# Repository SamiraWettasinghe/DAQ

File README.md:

# DAQ
Open source data acquisition system designed for the grassroots motorsports enthusiast.

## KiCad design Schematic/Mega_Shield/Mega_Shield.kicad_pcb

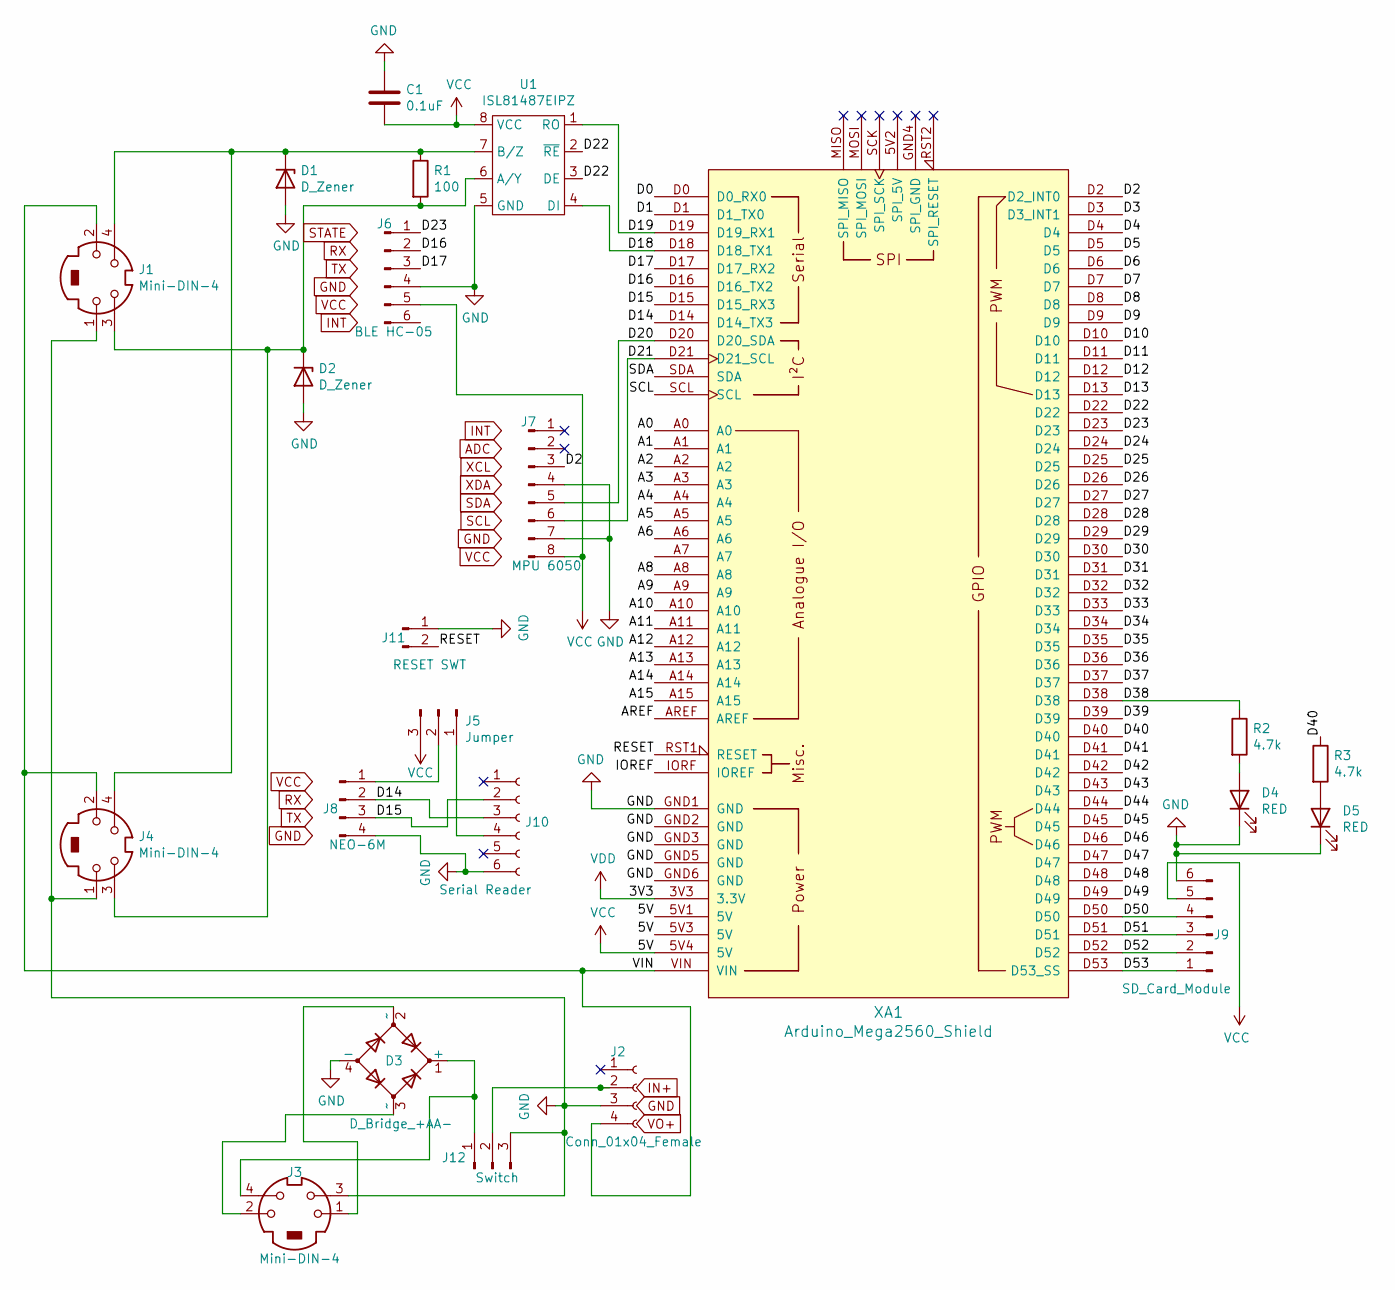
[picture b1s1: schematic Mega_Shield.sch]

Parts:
C1: 0.1uF; C_Rect_L4.0mm_W2.5mm_P2.50mm
D1, D2: D_Zener; D_DO-41_SOD81_P10.16mm_Horizontal
D3: D_Bridge_+AA-; KBP306GTB
D4, D5: RED; LED_3mm_Radial
J1, J3, J4: Mini-DIN-4; PinSocket_2x02_P2.54mm_Vertical
J2: Conn_01x04_Female; Voltage_Regulator
J5: Jumper; PinSocket_1x03_P2.54mm_Vertical
J6: BLE HC-05; BLEHC-05
J7: MPU 6050; GY-521
J8: NEO-6M
J9: SD_Card_Module; SD_Module_Vertical
J10: Serial Reader; PinSocket_1x06_P2.54mm_Vertical
J11: RESET SWT; PinSocket_1x02_P2.54mm_Vertical
J12: Switch; PinSocket_1x03_P2.54mm_Vertical
R1: 100; R_Axial_DIN0207_L6.3mm_D2.5mm_P7.62mm_Horizontal
R2, R3: 4.7k; R_Axial_DIN0204_L3.6mm_D1.6mm_P5.08mm_Horizontal
U1: ISL81487EIPZ; ISL81487EIPZ-PDIP
XA1: Arduino_Mega2560_Shield

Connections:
/A0: XA1.A0
/A1: XA1.A1
/A2: XA1.A2
/A3: XA1.A3
/A4: XA1.A4
/A5: XA1.A5
/A6: XA1.A6
/A8: XA1.A8
/A9: XA1.A9
/A10: XA1.A10
/A11: XA1.A11
/A12: XA1.A12
/A13: XA1.A13
/A14: XA1.A14
/A15: XA1.A15
/AREF: XA1.AREF
/D0: XA1.D0 (D0_RX0)
/D1: XA1.D1 (D1_TX0)
/D2: J7.3, XA1.D2 (D2_INT0)
/D3: XA1.D3 (D3_INT1)
/D4: XA1.D4
/D5: XA1.D5
/D6: XA1.D6
/D7: XA1.D7
/D8: XA1.D8
/D9: XA1.D9
/D10: XA1.D10
/D11: XA1.D11
/D12: XA1.D12
/D13: XA1.D13
/D14: J8.2, J10.3, XA1.D14 (D14_TX3)
/D15: J8.3, J10.2, XA1.D15 (D15_RX3)
/D16: J6.2, XA1.D16 (D16_TX2)
/D17: J6.3, XA1.D17 (D17_RX2)
/D18: U1.4 (DI), XA1.D18 (D18_TX1)
/D19: U1.1 (RO), XA1.D19 (D19_RX1)
/D20: J7.5, XA1.D20 (D20_SDA)
/D21: J7.6, XA1.D21 (D21_SCL)
/D22: U1.2 (~RE), U1.3 (DE), XA1.D22
/D23: J6.1, XA1.D23
/D24: XA1.D24
/D25: XA1.D25
/D26: XA1.D26
/D27: XA1.D27
/D28: XA1.D28
/D29: XA1.D29
/D30: XA1.D30
/D31: XA1.D31
/D32: XA1.D32
/D33: XA1.D33
/D34: XA1.D34
/D35: XA1.D35
/D36: XA1.D36
/D37: XA1.D37
/D38: R2.1, XA1.D38
/D39: XA1.D39
/D40: R3.1, XA1.D40
/D41: XA1.D41
/D42: XA1.D42
/D43: XA1.D43
/D44: XA1.D44
/D45: XA1.D45
/D46: XA1.D46
/D47: XA1.D47
/D48: XA1.D48
/D49: XA1.D49
/D50: J9.4, XA1.D50
/D51: J9.3, XA1.D51
/D52: J9.2, XA1.D52
/D53: J9.1, XA1.D53 (D53_SS)
/IOREF: XA1.IORF (IOREF)
/RESET: J11.2, XA1.RST1 (RESET)
/VIN: J1.2, J2.4, J4.2, XA1.VIN
GND: C1.1, D1.2 (A), D2.2 (A), D3.4 (-), D4.1 (K), D5.1 (K), J1.1, J2.3, J3.3, J4.1, J6.4, J7.4, J7.7, J8.4, J9.6, J10.6, J11.1, J12.3, U1.5 (GND), XA1.GND1 (GND), XA1.GND2 (GND), XA1.GND3 (GND), XA1.GND5 (GND), XA1.GND6 (GND)
unnamed: D1.1 (K), J1.4, J4.4, R1.1, U1.7 (B/Z)
unnamed: D2.1 (K), J1.3, J4.3, R1.2, U1.6 (A/Y)
unnamed: D3.1 (+), J3.4, J12.1
unnamed: D3.2 (~~), J3.1
unnamed: D3.3 (~~), J3.2
unnamed: D4.2 (A), R2.2
unnamed: D5.2 (A), R3.2
unnamed: J5.2, J8.1
unnamed: J5.1, J10.4
unnamed: J2.2, J12.2
SCL: XA1.SCL
SDA: XA1.SDA
VCC: C1.2, J5.3, J6.5, J7.8, J9.5, U1.8 (VCC), XA1.5V1 (5V), XA1.5V3 (5V), XA1.5V4 (5V)
VDD: XA1.3V3 (3.3V)

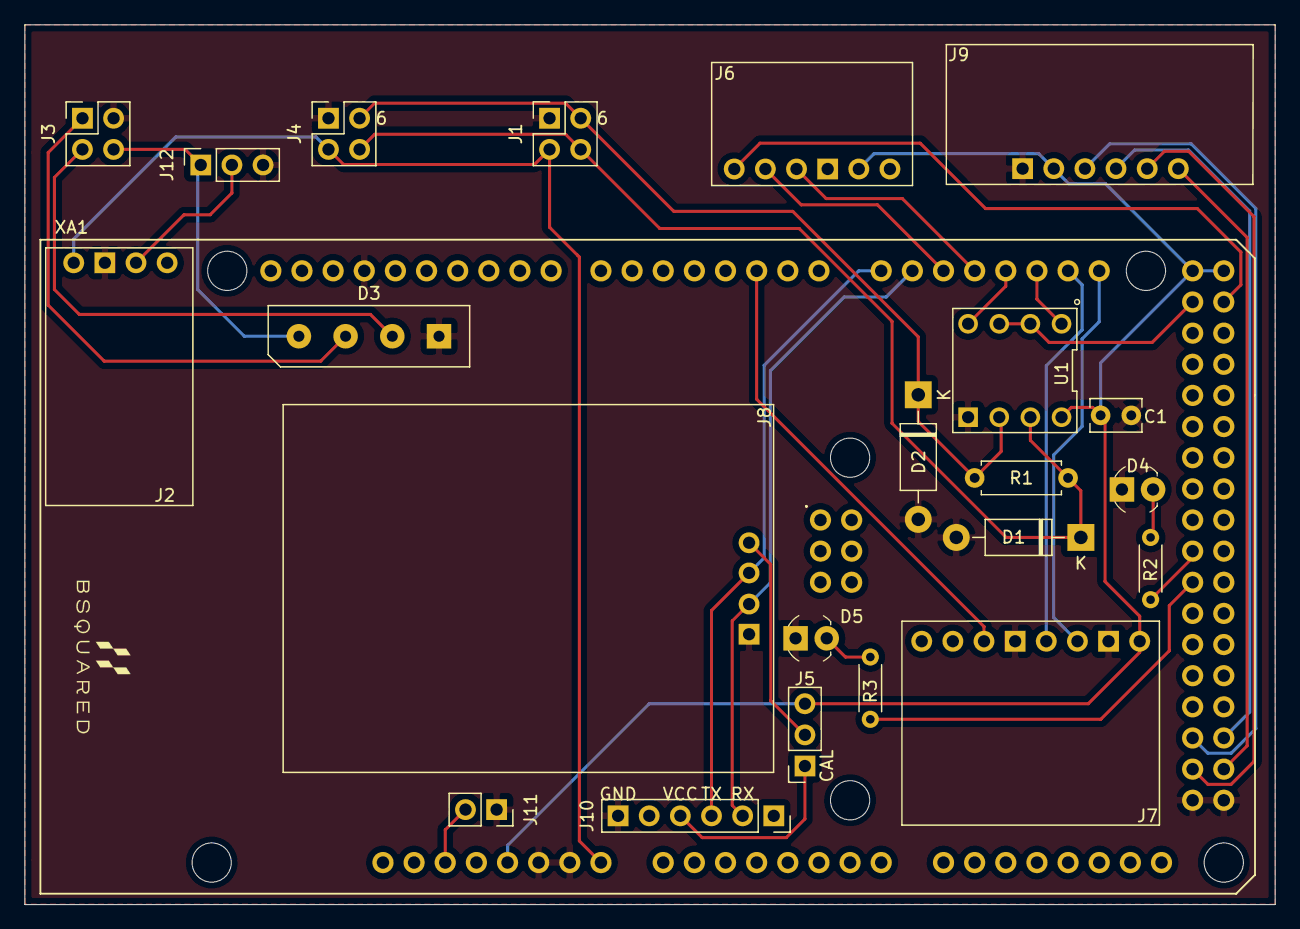
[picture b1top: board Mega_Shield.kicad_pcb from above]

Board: 2 copper layers, 102.0 x 71.8 mm, 23 parts (0 on the bottom side), 31 nets.

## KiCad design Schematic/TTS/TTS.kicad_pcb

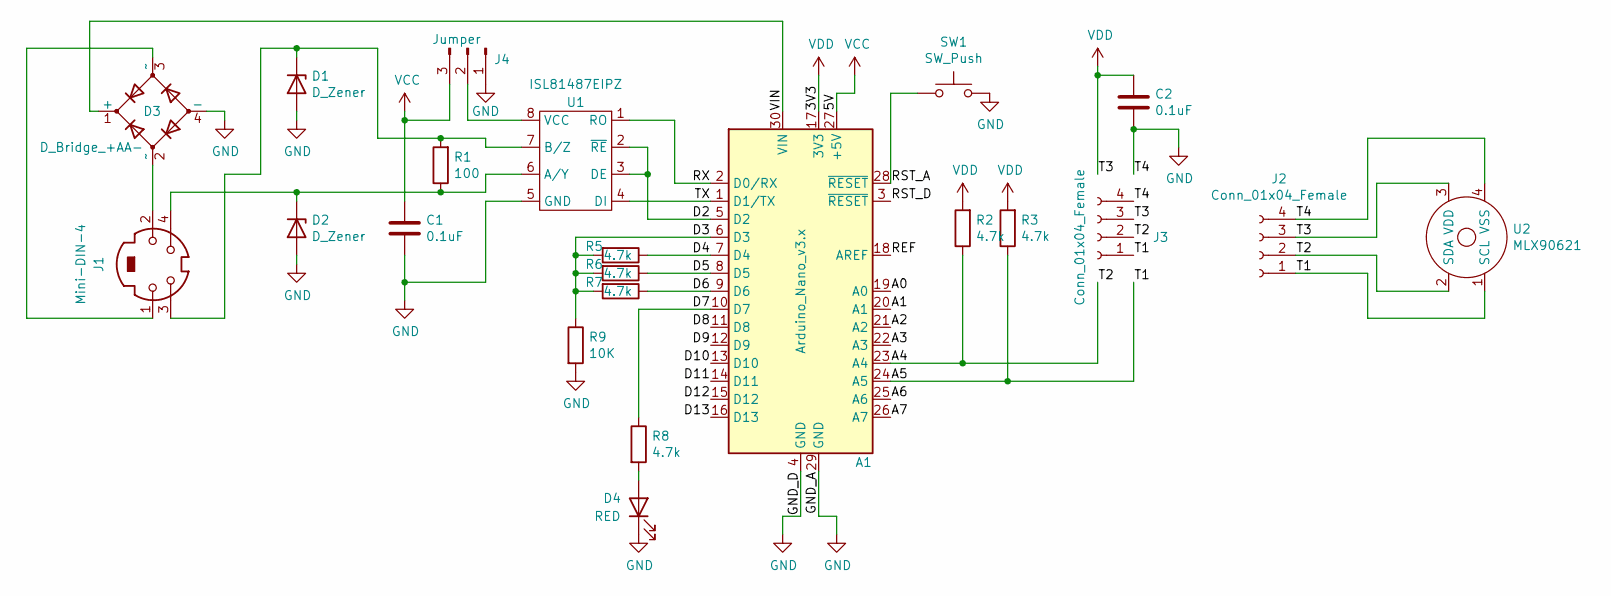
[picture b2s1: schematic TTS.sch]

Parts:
A1: Arduino_Nano_v3.x; Arduino_Nano
C1, C2: 0.1uF; C_Rect_L4.0mm_W2.5mm_P2.50mm
D1, D2: D_Zener; D_DO-41_SOD81_P10.16mm_Horizontal
D3: D_Bridge_+AA-; KBP306GTB
D4: RED; LED_3mm_Radial
J1: Mini-DIN-4; PinSocket_2x02_P2.54mm_Vertical
J2, J3: Conn_01x04_Female; PinSocket_1x04_P2.54mm_Vertical
J4: Jumper; PinSocket_1x03_P2.54mm_Vertical
R1: 100; R_Axial_DIN0309_L9.0mm_D3.2mm_P12.70mm_Horizontal
R2, R3, R5, R6, R7, R8: 4.7k; R_Axial_DIN0204_L3.6mm_D1.6mm_P5.08mm_Horizontal
R9: 10K; R_Axial_DIN0207_L6.3mm_D2.5mm_P7.62mm_Horizontal
SW1: SW_Push; PinSocket_1x02_P2.54mm_Vertical
U1: ISL81487EIPZ; ISL81487EIPZ-PDIP
U2: MLX90621; MLX90614ESF-BCC-000-TU

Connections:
/A0: A1.19 (A0)
/A1: A1.20 (A1)
/A2: A1.21 (A2)
/A3: A1.22 (A3)
/A4: A1.23 (A4), J2.2, J3.2, R2.1, U2.2 (SDA)
/A5: A1.24 (A5), J2.1, J3.1, R3.1, U2.1 (SCL)
/A6: A1.25 (A6)
/A7: A1.26 (A7)
/D2: A1.5 (D2), U1.2 (~RE), U1.3 (DE)
/D3: A1.6 (D3), R5.2, R6.2, R7.2, R9.1
/D4: A1.7 (D4), R5.1
/D5: A1.8 (D5), R6.1
/D6: A1.9 (D6), R7.1
/D7: A1.10 (D7), R8.1
/D8: A1.11 (D8)
/D9: A1.12 (D9)
/D10: A1.13 (D10)
/D11: A1.14 (D11)
/D12: A1.15 (D12)
/D13: A1.16 (D13)
/REF: A1.18 (AREF)
/RST_A: A1.28 (~RESET), SW1.1
/RST_D: A1.3 (~RESET)
/RX: A1.2 (D0/RX), U1.1 (RO)
/TX: A1.1 (D1/TX), U1.4 (DI)
/VIN: A1.30 (VIN), D3.1 (+)
GND: A1.4 (GND), A1.29 (GND), C1.2, C2.2, D1.2 (A), D2.2 (A), D3.4 (-), D4.1 (K), J2.4, J3.4, J4.1, R9.2, SW1.2, U1.5 (GND), U2.4 (VSS)
unnamed: D1.1 (K), J1.3, R1.2, U1.7 (B/Z)
unnamed: D2.1 (K), J1.4, R1.1, U1.6 (A/Y)
unnamed: D3.2 (~~), J1.2
unnamed: D3.3 (~~), J1.1
unnamed: D4.2 (A), R8.2
unnamed: J4.2, U1.8 (VCC)
VCC: A1.27 (+5V), C1.1, J4.3
VDD: A1.17 (3V3), C2.1, J2.3, J3.3, R2.2, R3.2, U2.3 (VDD)

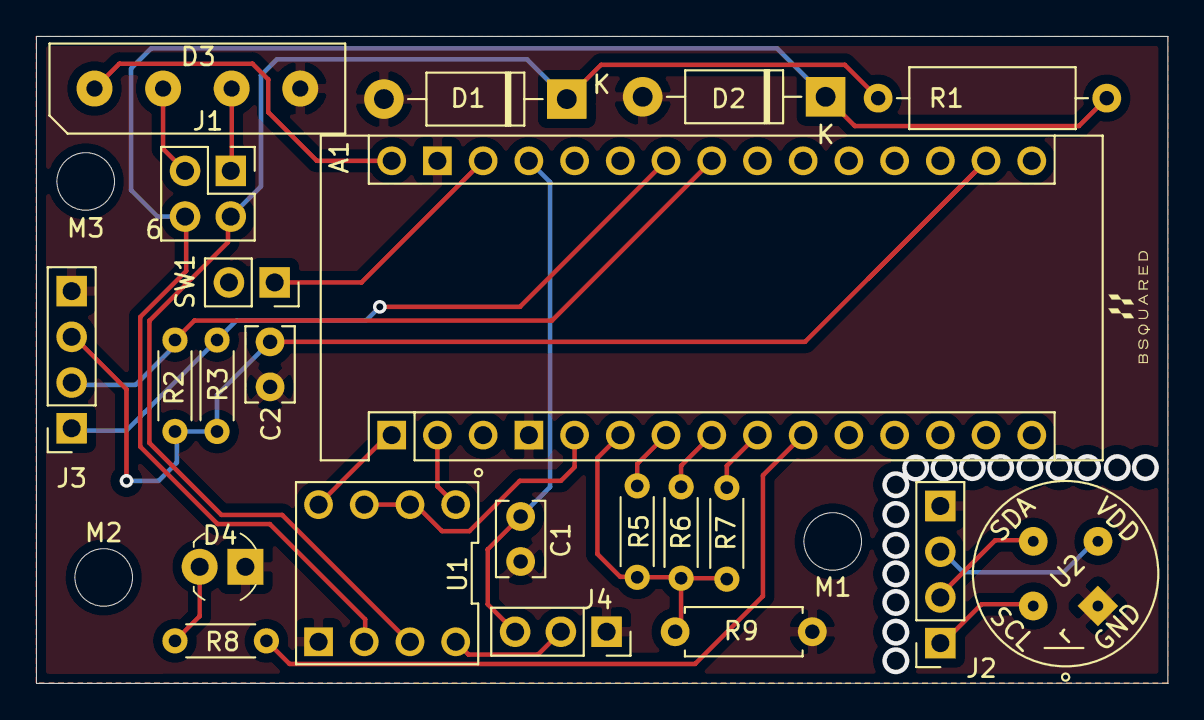
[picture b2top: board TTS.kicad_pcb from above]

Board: 2 copper layers, 62.9 x 35.9 mm, 25 parts (0 on the bottom side), 21 nets.

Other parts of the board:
M1, M2, M3: MountingHole_3.2mm_M3

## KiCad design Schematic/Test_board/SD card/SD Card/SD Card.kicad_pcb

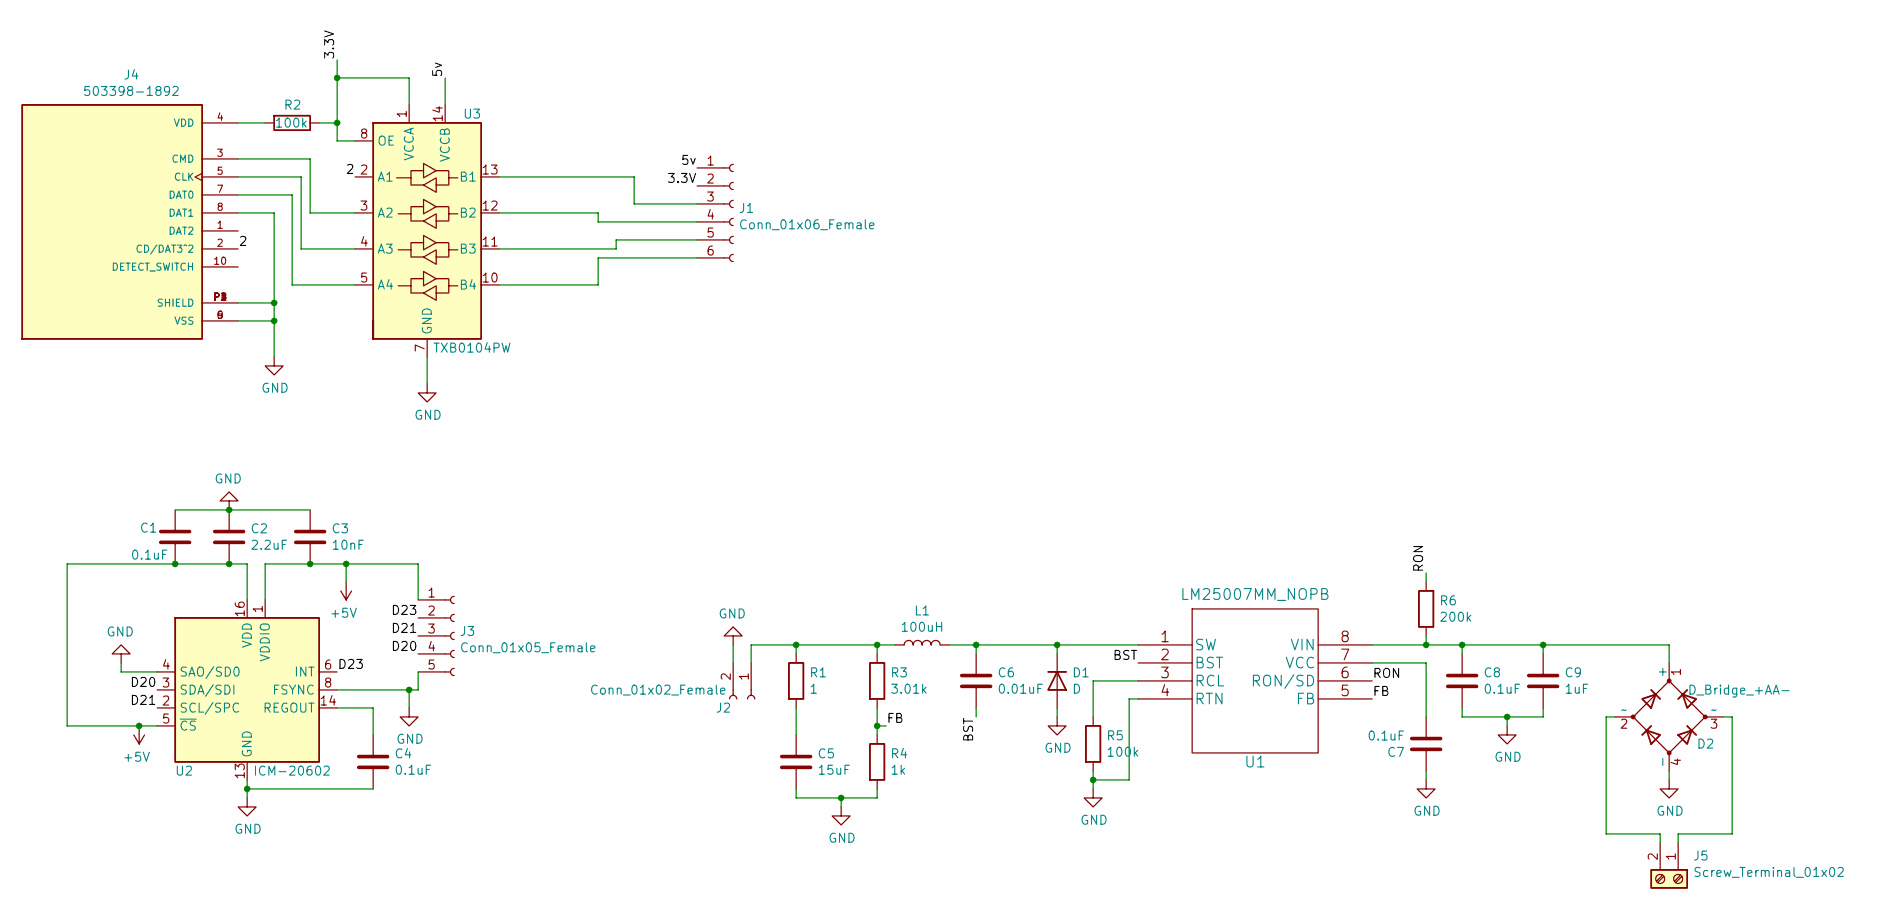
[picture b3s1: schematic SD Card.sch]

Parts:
C1, C4: 0.1uF; CP_Radial_D5.0mm_P2.50mm
C2: 2.2uF; CP_Radial_D5.0mm_P2.50mm
C3: 10nF; CP_Radial_D5.0mm_P2.50mm
C5: 15uF; C_1812_4532Metric_Pad1.57x3.40mm_HandSolder
C6: 0.01uF; C_1206_3216Metric_Pad1.33x1.80mm_HandSolder
C7, C8: 0.1uF; C_1206_3216Metric_Pad1.33x1.80mm_HandSolder
C9: 1uF; C_1812_4532Metric_Pad1.57x3.40mm_HandSolder
D1: D; D_SMA_Handsoldering
D2: D_Bridge_+AA-; KBP306GTB
J1: Conn_01x06_Female; PinHeader_1x06_P2.54mm_Vertical
J2: Conn_01x02_Female; PinHeader_1x02_P2.54mm_Vertical
J3: Conn_01x05_Female; PinHeader_1x05_P2.54mm_Vertical
J4: 503398-1892; MOLEX_503398-1892; PARTREV 0
J5: Screw_Terminal_01x02; TerminalBlock_Phoenix_PT-1,5-2-5.0-H_1x02_P5.00mm_Horizontal
L1: 100uH; L_TDK_SLF7045
R1: 1; R_1206_3216Metric_Pad1.30x1.75mm_HandSolder
R2: 100k; R_Axial_DIN0204_L3.6mm_D1.6mm_P5.08mm_Horizontal
R3: 3.01k; R_1206_3216Metric_Pad1.30x1.75mm_HandSolder
R4: 1k; R_1206_3216Metric_Pad1.30x1.75mm_HandSolder
R5: 100k; R_1206_3216Metric_Pad1.30x1.75mm_HandSolder
R6: 200k; R_1206_3216Metric_Pad1.30x1.75mm_HandSolder
U1: LM25007MM_NOPB; LM25007MM&slash_NOPB
U2: ICM-20602; LGA-16_3x3mm_P0.5mm_LayoutBorder3x5y
U3: TXB0104PW; TSSOP-14_4.4x5mm_P0.65mm

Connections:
+5V: C1.2, C2.2, C3.2, J3.1, U2.1 (VDDIO), U2.5 (~CS), U2.16 (VDD)
/2: J4.2 (CD/DAT3^2), U3.2 (A1)
/3.3V: J1.2, R2.1, U3.1 (VCCA), U3.8 (OE)
/5v: J1.1, U3.14 (VCCB)
/BST: C6.2, U1.2 (BST)
/D20: J3.4, U2.3 (SDA/SDI)
/D21: J3.3, U2.2 (SCL/SPC)
/D23: J3.2, U2.6 (INT)
/FB: R3.2, R4.1, U1.5 (FB)
/RON: R6.2, U1.6 (RON/SD)
GND: C1.1, C2.1, C3.1, C4.2, C5.2, C7.1, C8.2, C9.2, D1.2 (A), D2.4 (-), J2.2, J3.5, J4.6 (VSS), J4.8 (DAT1), J4.9 (VSS), J4.P1 (SHIELD), J4.P2 (SHIELD), J4.P3 (SHIELD), J4.P4 (SHIELD), R4.2, R5.2, U1.4 (RTN), U2.4 (SAO/SD0), U2.8 (FSYNC), U2.9 (GND), U2.10 (GND), U2.11 (GND), U2.12 (GND), U2.13 (GND), U2.15 (GND), U3.7 (GND)
unnamed: C4.1, U2.14 (REGOUT)
unnamed: C5.1, R1.2
unnamed: C6.1, D1.1 (K), L1.2, U1.1 (SW)
unnamed: C7.2, U1.7 (VCC)
unnamed: C8.1, C9.1, D2.1 (+), R6.1, U1.8 (VIN)
unnamed: D2.2 (~~), J5.2
unnamed: D2.3 (~~), J5.1
unnamed: J1.3, U3.13 (B1)
unnamed: J1.4, U3.12 (B2)
unnamed: J1.5, U3.11 (B3)
unnamed: J1.6, U3.10 (B4)
unnamed: J2.1, L1.1, R1.1, R3.1
unnamed: J4.3 (CMD), U3.3 (A2)
unnamed: J4.4 (VDD), R2.2
unnamed: J4.5 (CLK), U3.4 (A3)
unnamed: J4.7 (DAT0), U3.5 (A4)
unnamed: R5.1, U1.3 (RCL)

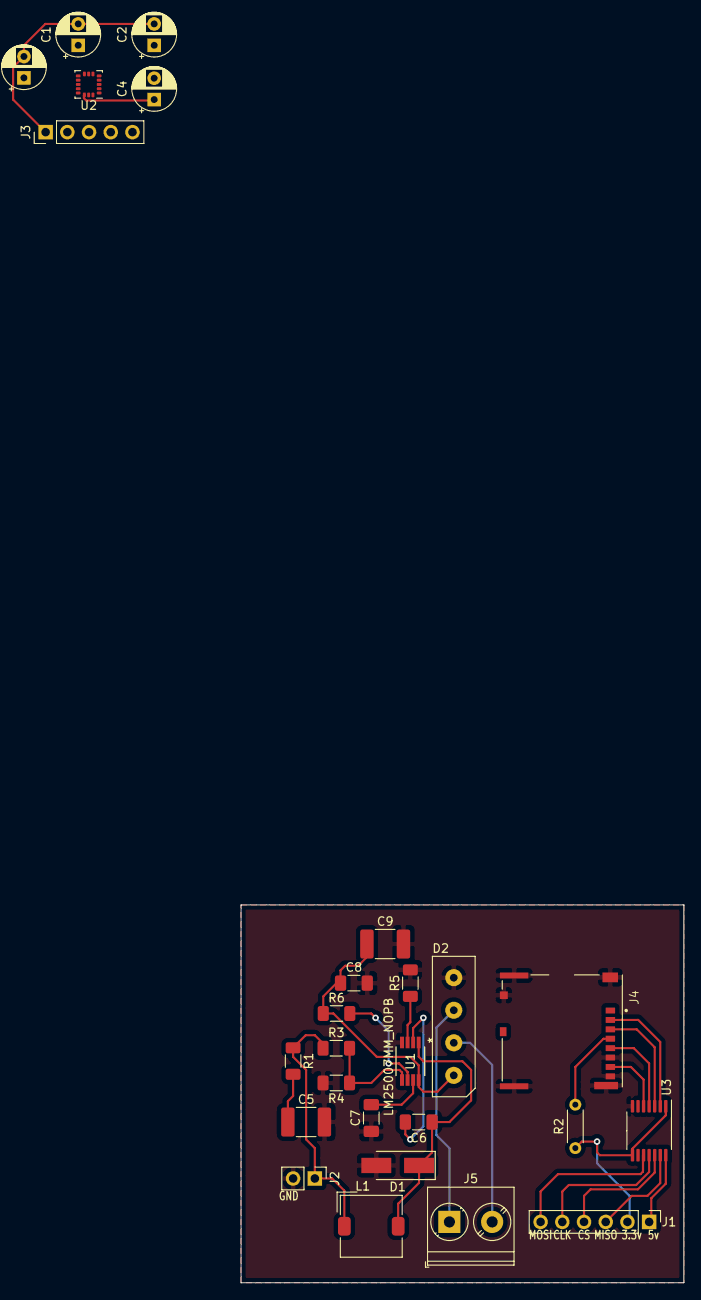
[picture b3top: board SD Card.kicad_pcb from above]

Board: 2 copper layers, 51.8 x 44.2 mm, 26 parts (0 on the bottom side), 28 nets.

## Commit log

2020-08-13 Added OBDii data.
    Through OBD, added capability to read vehicle speed and RPM. Work still needs to be done to send CAN frames to Mega successfully. OBD is accessed through Sparkfun's UART.
    Vehicle CAN Project - Investigation
2020-08-18 Initial commit of accelerometer code.
    Added code to interface to MPU-6050. Code is from playgroud.arduino.cc/Main/MPU-6050. Raw values of accel, gyro, and temperature are recorded and sent through serial monitor.
    Accelerometer investigation
2020-08-19 Added CAN communication for OBD-II data.
    Modified obdii file to send vehicle speed and RPM over CAN. Also added code on receive module to receive CAN data from obdii module. CAN ID for obdii is 0x05.
    OBD-II Data Integration
2020-08-20 Added dual accelerometer comms
    Set up ADO pin to ground for one sensor and 3.3V for the other sensor such that the sensors can have different addresses (0x68 and 0x69).
    Accelerometer and Gyrometer Investigation
2020-08-21 GPS and SD card data logger
    Ubloc Neo-6m GPS module is used - Pin 2 and 3 is as TX and RX reader
    Mirco SD card adapter module is connected with the following Pin IDs Vcc to 5v, MISO to pin 12 (50), MOSI to Pin 11 (51), SCK to pin 13 (52) and CS to Pin 4 (53). Note for Arduino UNO use Pin ID with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
2020-08-21 Organization and documentation and added CAN comms
    Created GPS folder to store the GPS code. Created integration documentation for accelerometer and the OBD-II data. Added CAN comms for the accelerometer data. 0x06 for linear acceleration and 0x07 fo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
    Accelerometer and Gyrometer Investigation
2020-09-15 Added SD Card integration.
    SD card is commmunicating via UART with Mega. Currently sending only accelerometer data.
    First evaluation day - Samira Wettasinghe
2020-09-17 Changed to SPI comms for SD card
    SPI comms working for SD card storage. No issues since CS is D11 while tire temps are on D12.
    SD Card Comms - Samira Wettasinghe
2020-09-21 Added timestamp
    CAN transmits timestamp. SD card will store timestamp in hour minute millisecond format.
    Timestamp transmission - Samira Wettasinghe
2020-09-22 Tire temp timestamp coherency
    Added simple coherency check.
    Modified delays to be as short as possible to avoid filling the buffer.
    Created functions to clean up code.
    Timestamp transmission - Samira Wettasinghe
2020-09-26 Integrated GPS code. General cleanup.
    GPS code is integrated. Added hardware present calibrations. Cleaned up code to ensure that it works properly when all sensors are presnet. Removed some of the time stamp coherency checks for now, ad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
    Installation Day 2 - Samira Wettasinghe
2020-09-29 Fixed OBD logging. Added system arch doc.
    OBD logging now done properly and logging quickly. Created initial revision of architecture document. Feature revisions made for Mega code as well.
    V2 Testing - Samira Wettasinghe
2020-10-25 Added PCB designs
    Adding PCB design of Mega shield and tire temp sensors.
    Samira Wettasinghe
2020-10-30 Antul is amazing
    Antul literally is so smart. Everytime we have an issue, and he has a suggestion, he is always correct. Amando agrees.
    Preach Antul - Samira Wettasinghe
2020-10-30 Git Training
    Useful File
    Git Training - Samira Wettasinghe
2020-10-30 Git training
2020-11-12 Updating schematic with Oshpark/Digikey order
    Updates to add various components and capability.
    2.2 Basic Sensor Suite
2020-11-12 Differential wire concept
    Testing concept with serial comms.
    2.2 Basic Sensor Suite
2020-11-17 DIP switch and status LED and IMU code integrated
    Added code to read from DIP switch and LED digital pins. IMU code added on mega shield. No data can be read on the i2c due to incorrect SCL/SDA pins being connected to IMU.
    2.2 Basic Sensor Suite
2020-11-18 SD Card logging code added.
    SD card logic was added. CS may need modification based on new PCB design. This code will need to be tested.
    2.2 Basic Sensor Suite
2020-11-20 Fixed schematic issues. Made code for TTS transmit
    Schematic issues documented on Trello card fixed. TTS differential wire transmit code for the TTS implemented. Still need to do auto adressing and time stamp transmission.
    2.2 Basic Sensor Suite
2020-12-03 Verified UART comms.
    Made sure that UART was working with two sensors communicating with Mega.
    2.2 Basic Sensor Suite
2020-12-10 Integration of IMU + comms algo upgrade.
    Upgraded comms method to use switch/case method. Integrade the IMU board onto the Mega shield.
    2.2 Basic Sensor Suite
2020-12-15 Added diagnostic messages and error codes
    Added serial data print messages if data received doesn't make sense.
    Added error codes that will print to the data.
    Added LED for indicate an error has set.
    2.7 Diagnostic Software
2020-12-16 test board PCB design
    PCB include SD card and IMU
    2.2 Basic Sensor Suite
2020-12-17 test board PCB design
    PCB includes SD card and IMU
    2.2 Basic Sensor Suite
2020-12-17 Added power distribution to test board.
    Added the schematic and footprints needed for power distribution in test board.
    2.2. Basic Sensor Suite
2020-12-18 Test board PCB design
    Board includes SD card, IMU and PDU
    2.2 Basic Sensor Suite
2021-02-01 Implemented scheduler for consistent logging rates
    Scheduled the execution of the functions to ensure that data is stored at a reliable run rate.
    2.2 Basic Sensor Suite
2021-02-11 Upadeted PCB design for Logger and for TTS
    Mega updated for BLE and reduced in size. Nano shield updated for
    MLX90621 array based sensor
2021-02-11 Test code added for New logger and TTS design
    Test code created to test bluetooth comunication to RaceChrono, MLX90621
    array based sensr and to test the PCB trace with individual modules,
    GPS, IMU and SD card.
2021-02-16 Udated logger and TTS for full sensor suit
    2.2 Basic Sensor Suit and 2.6 Array Based Tire Temps
2021-03-08 Verion 4 PCB and Code
    Updated PCB layout for version 4; for both TTS and Logger.
    Updated code to asign ID to TTS and to send data via BT

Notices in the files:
parts and their libraries:
Copyright 2016 Accelerated Designs. All rights reserved.
